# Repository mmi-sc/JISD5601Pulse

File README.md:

# JISD5601Pulse
JIS D 5601 Speed Pulse Generator

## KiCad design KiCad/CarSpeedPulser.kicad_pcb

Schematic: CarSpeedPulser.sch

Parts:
C1, C2, C3, C4, C5: 1u; C_0805_HandSoldering
D1: LED; LED_1206_3216Metric_Pad1.07x1.80mm_HandSolder
D2, D3: 1N4148W; SOD-123
P1: CONN_01X03; Socket_Strip_Angled_1x03
P2: CONN_01X05; Pin_Header_Straight_1x05
Q1: RUE002N02; EMT3
R1: 1k; R_0603_1608Metric_Pad0.84x1.00mm_HandSolder
R2: 1M; R_0603_1608Metric_Pad0.84x1.00mm_HandSolder
R3: 680; R_0603_1608Metric_Pad0.84x1.00mm_HandSolder
R4, R5: 10k; R_0603_1608Metric_Pad0.84x1.00mm_HandSolder
R6: 1M; R_0603_HandSoldering
SW1: RESET; Elko_vert_11.2x6.3mm_RM2.5
SW2: UP; Elko_vert_11.2x6.3mm_RM2.5
SW3: DOWN; Elko_vert_11.2x6.3mm_RM2.5
U1: LPC810; DIP-8_W7.62mm
U2: AQM0802A-RN-GBW
U3: NJM78L33SU3; SOT-89-3_Handsoldering
U4: R3111N211A; SOT-23-5_HandSoldering

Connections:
+12V: D2.2, P1.1
/#RST: P2.1, R6.1, SW1.1, U1.1, U4.1
/CAP1N: C5.1, U2.3
/CAP1P: C5.2, U2.4
/D: P1.2, Q1.3
/GATE: Q1.2, R1.1, R2.1
/PIO0_2: SW3.1, U1.4
/PIO0_3: SW2.1, U1.3
/PIO0_4: P2.2, R1.2, R3.2, U1.2
/SCL: P2.4, R4.1, U1.8, U2.8
/SDA: P2.3, R5.1, U1.5, U2.7
/VOUT: C4.1, U2.2
/VSS: C1.2, C2.2, C3.2, D1.1, D3.2, P2.5, Q1.1, R2.2, SW1.2, SW2.2, SW3.2, U1.7, U2.6, U3.2, U4.3
/Vin: C1.1, D2.1, U3.3
unnamed: D1.2, R3.1
unnamed: D3.1, P1.3
VDD: C2.1, C3.1, C4.2, R4.2, R5.2, R6.2, U1.6, U2.5, U2.9, U3.1, U4.2

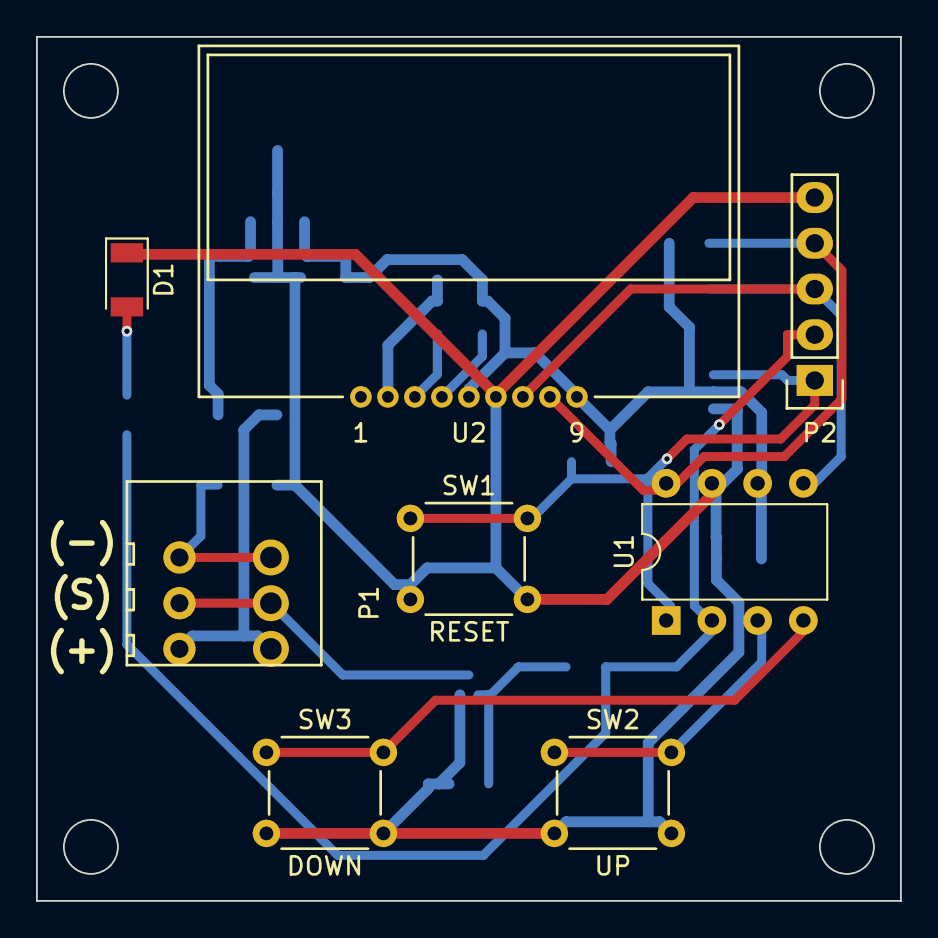
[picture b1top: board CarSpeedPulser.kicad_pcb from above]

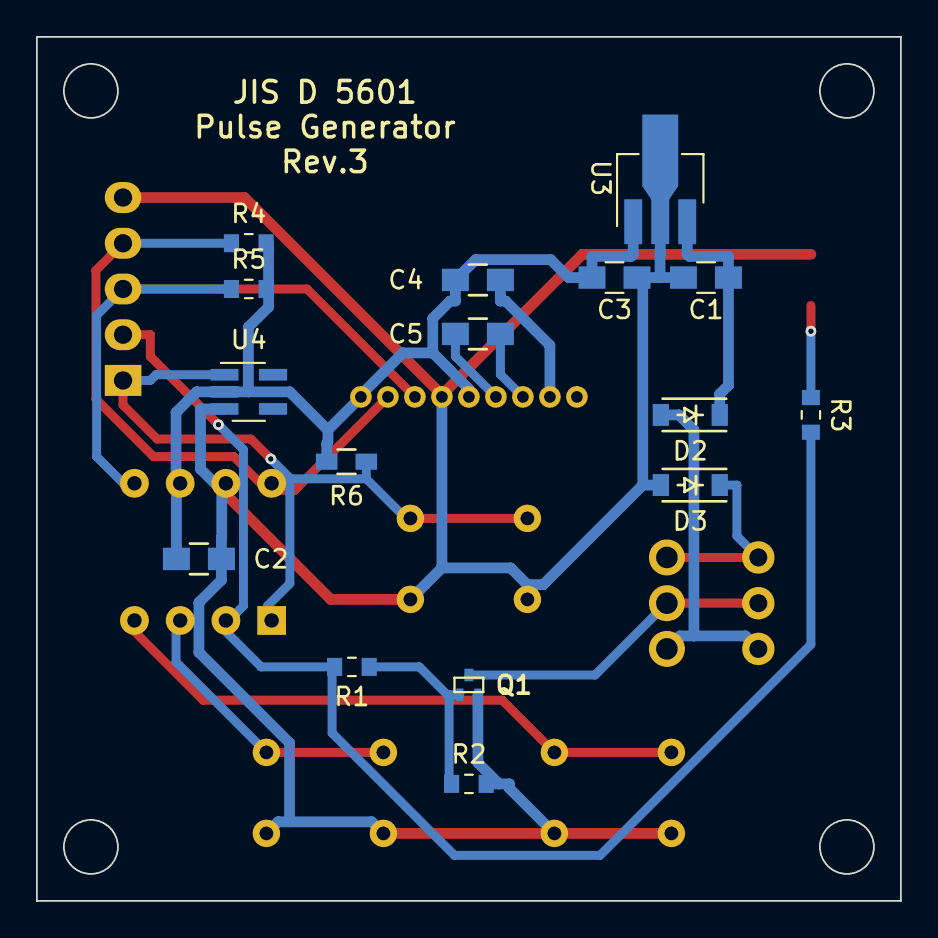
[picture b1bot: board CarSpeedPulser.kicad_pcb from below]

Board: 2 copper layers, 48.0 x 48.0 mm, 24 parts (16 on the bottom side), 17 nets.

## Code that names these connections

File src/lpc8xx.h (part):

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  __IO uint32_t PIO0_13;                    /*!< (@ 0x40044004) I/O configuration for pin PIO0_13 */
  __IO uint32_t PIO0_12;                    /*!< (@ 0x40044008) I/O configuration for pin PIO0_12 */
  __IO uint32_t PIO0_5;                     /*!< (@ 0x4004400C) I/O configuration for pin PIO0_5 */
  __IO uint32_t PIO0_4;                     /*!< (@ 0x40044010) I/O configuration for pin PIO0_4 */
  __IO uint32_t PIO0_3;                     /*!< (@ 0x40044014) I/O configuration for pin PIO0_3 */
  __IO uint32_t PIO0_2;                     /*!< (@ 0x40044018) I/O configuration for pin PIO0_2 */
  __IO uint32_t PIO0_11;                    /*!< (@ 0x4004401C) I/O configuration for pin PIO0_11 */
  __IO uint32_t PIO0_10;                    /*!< (@ 0x40044020) I/O configuration for pin PIO0_10 */
  __IO uint32_t PIO0_16;                    /*!< (@ 0x40044024) I/O configuration for pin PIO0_16 */
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
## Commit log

2015-05-06 Imported LPCXPresso project.
2015-05-16 Create from minimum source.
2015-05-17 Blink a LED slowly by SCT.
2015-05-17 ボタンによる指令が不調。
2015-05-17 It's buggy. Strange behavior.
2015-05-17 It worked fine.
2015-05-18 Added KiCad PCB data.
2015-05-18 Initialize I2C LCD before GPIO.
2015-05-18 Added writer connector.
2015-05-18 Added Switch Matrix Tool output.
2015-05-18 Clear second line of LCD.
2015-05-19 Updated circuit diagram.
2015-05-19 Convert to ihex.
2015-05-21 Step downed optional pulse rates.
2015-05-21 Correct values of capacitors.
2015-05-22 Replaced a connector.
2015-11-05 Removed pullup register. PULSE output is open drain.
2015-11-09 Replaced AE-AQM802 with AQM0802A-RN-GBW.
2015-11-09 Changed footprint of a speaker.
2015-11-10 Added a footprint of terminal block.
2015-11-10 Replaced footprint of AQM0802A-RN-GBW.
2015-11-10 Added footprint of piezo speaker.
2015-11-15 Replaced voltage regulator to SMD type.
2015-12-02 Show pulse per rotation on second line.
2016-01-25 Added diodes, registers and a voltage detector.
2016-04-06 Changed directory name of 3D shapes.
2016-09-24 Adjust contrast value.
2017-09-26 Added LICENSE
2017-09-26 Updated KiCad parts library
2017-09-26 Replaced 3.3V regulator
2017-09-26 Use LPCOpen Software Development Platform LPC8XX
2017-09-26 Updated parts library
2017-09-27 Removed unused reference to lpc800_driver_lib project
2017-10-03 Replaced voltage detector
2017-10-07 Replaced 3D models path
    Replaced 3D models path.
    Removed unused footprints.
2018-09-03 Migrated to KiCad 5.0
2018-09-11 Added counter frequency formula
2018-09-11 Added MCUXpresso Config Tools output

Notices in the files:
src/lpc8xx.h:
Copyright(C) NXP Semiconductors, 2012
All rights reserved.
